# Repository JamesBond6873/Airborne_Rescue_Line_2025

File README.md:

<div align="center">

</div>

<br/>

<p align="center">
  This is the repository for <strong>Airborne</strong>, a Portuguese robotics team that participated in the
  <a href="https://junior.robocup.org/">RoboCup Junior</a> sub-league
  <a href="https://junior.robocup.org/rcj-rescue-line/">Rescue Line</a>.
</p>

# About the Competition
<p align="center"><i>
  "The land is too dangerous for humans to reach the victims. Your team has been given a challenging task. The robot must be able to carry out a rescue mission in a fully autonomous mode with no human assistance. The robot must be durable and intelligent enough to navigate treacherous terrain with hills, uneven land, and rubble without getting stuck. When the robot reaches the victims, it has to gently and carefully transport each one to the safe evacuation point where humans can take over the rescue. The robot should exit the evacuation zone after a successful rescue to continue its mission throughout the disaster scene until it leaves the site. Time and technical skills are essential!"
</i></p>

<div align="center">
  
</div>

# About the Robot

<!-- First block: Image on the left -->

<p align="justify">
  Our robot was built to reliably complete all challenges of the RoboCup Junior Rescue Line competition through a combination of computation, custom electronics, and mechanical design. It uses a dual-processor architecture: a Raspberry Pi 5 for high-level logic and AI, and a Raspberry Pi Pico for real-time control of motors and sensors. A Google Coral USB Accelerator enables onboard execution of two YOLOv8 models, one for victim detection and another for identifying the silver evacuation zone, which provide fast and accurate results compared to traditional computer vision.
</p>

<br/>

<!-- Second block: Image on the right -->

<p align="justify">
  The chassis was entirely designed in SolidWorks and 3D printed, with over 70 custom parts and a modular structure that simplifies maintenance. A tilt-mounted wide-angle camera, passive suspension system, and dual-servo rescue arm ensure strong performance across rough terrain. Internally, custom PCBs manage power distribution and sensor integration, keeping the system reliable and clean, with a much lower risk of lose wires. Software processes run in parallel for serial communication between boards, image processing, and control/decision-making, supported by a custom HTML/Websocket interface for real-time monitoring and debugging.
</p>

<br/>

<p align="center">
  As required by the competition <a href="https://github.com/JamesBond6873/Airborne_Rescue_Line_2025/blob/main/Documents/Rules/000_RoboCup_Junior_Rescue_Line_Rules_2025.pdf">rules</a>, in addition to this GitHub Repository, we created detailed documentation of the robot and our development process in the form of a <a href="https://github.com/JamesBond6873/Airborne_Rescue_Line_2025/blob/main/Documents/Final%20Rubrics/00_Airborne_TDP_RoboCup_Rescue_Line_2025.pdf">Technical Description Paper</a>, a <a href="https://github.com/JamesBond6873/Airborne_Rescue_Line_2025/blob/main/Documents/Final%20Rubrics/01_Airborne_Poster_RoboCup_Rescue_Line_2025.pdf">Technical Poster</a>, and a <a href="https://github.com/JamesBond6873/Airborne_Rescue_Line_2025/blob/main/Documents/Final%20Rubrics/02_Airborne_Video_RoboCup_Rescue_Line_2025_Compressed.mp4">Presentation Video</a>.
</p>

## 📂 Components

- Raspberry Pi 5 8GB Ram
- Raspberry Pi Pico
- Google Coral USB Accelerator
- Raspberry Pi Camera Module V3 Wide
- 5x VL53L0X ToF
- ICM-20948 9DOF IMU
- TCA9458 Multiplexer
- 4x Home-made Silicone Wheels
- 4x 12V 77RPM DC Geared Motors
- 4x 3S ESCs
- 6x SG90 MicroServos
- PCA9685 Servo Driver
- 2x Custom Led Bar PCB
- DRV8833 Power Driver
- Gens Ace 3S 2700mAh Lipo Battery
- D24V50F5 Step Down
- D36V28F5 Step Down

<br/>

## 🧠 Repository Structure

<p align="justify"> 
  This repository contains all the files developed and used throughout our RoboCup Junior Rescue Line project.
</p>

  - <code>RobotCode_Field_Version</code>: Contains the latest version of the code used in the official Field Runs
  - <code>RobotCode_TC_Version</code>: Contains the version used during the Technical Challenge run
  - <code>Ai</code>: Contains the versions of the YoloV8 Small Models used for victim and silver strip detections
  - <code>Documents</code>:
      - <code>Final Rubrics</code>: Contains our final three evaluated documents: Team Description Paper, Technical Poster and  Presentation Video (compressed)
      - <code>Rules</code>: Contains all official competition rulebooks (Rescue Line, Technical Challenge, SuperTeams), as well as the corresponding rubrics and templates for the documents
      - <code>scores</code>:  Contains the final scores from the RoboCup Junior World Championship 2025, in Salvador, Brazil

<br/>

# 🔗 Useful Links

- [Airborne Photo/Video Album](https://drive.google.com/drive/folders/1JC7H4FIJUuHvwdzJ9MUNMwsvkezMXKDg?usp=drive_link)
- [Technical Description Paper](https://drive.google.com/file/d/1SsVflj773ZcgajpcdkzmWjwUXBWZYv1-/view?usp=drive_link)
- [Technical Poster](https://drive.google.com/file/d/1fPJXqmR9CHxOLH45z3VVppOXiR5PiPfq/view?usp=drive_link)
- [Presentation Video](https://drive.google.com/file/d/1rCQD-FLG8RNpqSPlJDvGeZCaVhfCN_2y/view?usp=drive_link)
- [Rescue Line Rules 2025](https://github.com/JamesBond6873/Airborne_Rescue_Line_2025/blob/main/Documents/Rules/000_RoboCup_Junior_Rescue_Line_Rules_2025.pdf)
- [Airborne Instagram Account](https://www.instagram.com/airborne_2023/)

<br/>
<br/>

# 🤝 Sponsors

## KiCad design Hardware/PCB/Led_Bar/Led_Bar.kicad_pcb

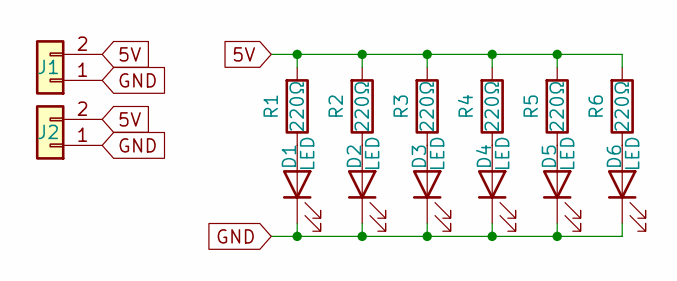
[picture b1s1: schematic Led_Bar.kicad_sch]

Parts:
D1, D2, D3, D4, D5, D6: LED; LED_D5.0mm
J1, J2: Conn_01x02; PinHeader_1x02_P2.54mm_Vertical
R1, R2, R3, R4, R5, R6: 220Ω; R_Axial_DIN0207_L6.3mm_D2.5mm_P2.54mm_Vertical

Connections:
5V: J1.2, J2.2, R1.2, R2.2, R3.2, R4.2, R5.2, R6.2
GND: D1.1 (K), D2.1 (K), D3.1 (K), D4.1 (K), D5.1 (K), D6.1 (K), J1.1, J2.1
unnamed: D1.2 (A), R1.1
unnamed: D2.2 (A), R2.1
unnamed: D3.2 (A), R3.1
unnamed: D4.2 (A), R4.1
unnamed: D5.2 (A), R5.1
unnamed: D6.2 (A), R6.1

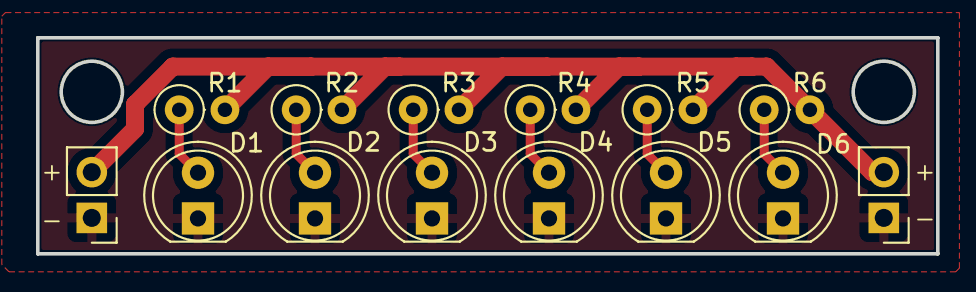
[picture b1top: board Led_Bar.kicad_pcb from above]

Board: 2 copper layers, 50.0 x 12.0 mm, 14 parts (0 on the bottom side), 8 nets.

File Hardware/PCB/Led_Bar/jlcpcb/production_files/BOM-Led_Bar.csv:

Comment,Designator,Footprint,LCSC,Quantity
220Ω,R6,R_Axial_DIN0207_L6.3mm_D2.5mm_P2.54mm_Vertical,,1
LED,D1,LED_D5.0mm,,1
220Ω,R1,R_Axial_DIN0207_L6.3mm_D2.5mm_P2.54mm_Vertical,,1
LED,D2,LED_D5.0mm,,1
220Ω,R2,R_Axial_DIN0207_L6.3mm_D2.5mm_P2.54mm_Vertical,,1
LED,D3,LED_D5.0mm,,1
220Ω,R3,R_Axial_DIN0207_L6.3mm_D2.5mm_P2.54mm_Vertical,,1
LED,D4,LED_D5.0mm,,1
220Ω,R4,R_Axial_DIN0207_L6.3mm_D2.5mm_P2.54mm_Vertical,,1
LED,D5,LED_D5.0mm,,1
220Ω,R5,R_Axial_DIN0207_L6.3mm_D2.5mm_P2.54mm_Vertical,,1
LED,D6,LED_D5.0mm,,1
Conn_01x02,J1,PinHeader_1x02_P2.54mm_Vertical,,1
Conn_01x02,J2,PinHeader_1x02_P2.54mm_Vertical,,1

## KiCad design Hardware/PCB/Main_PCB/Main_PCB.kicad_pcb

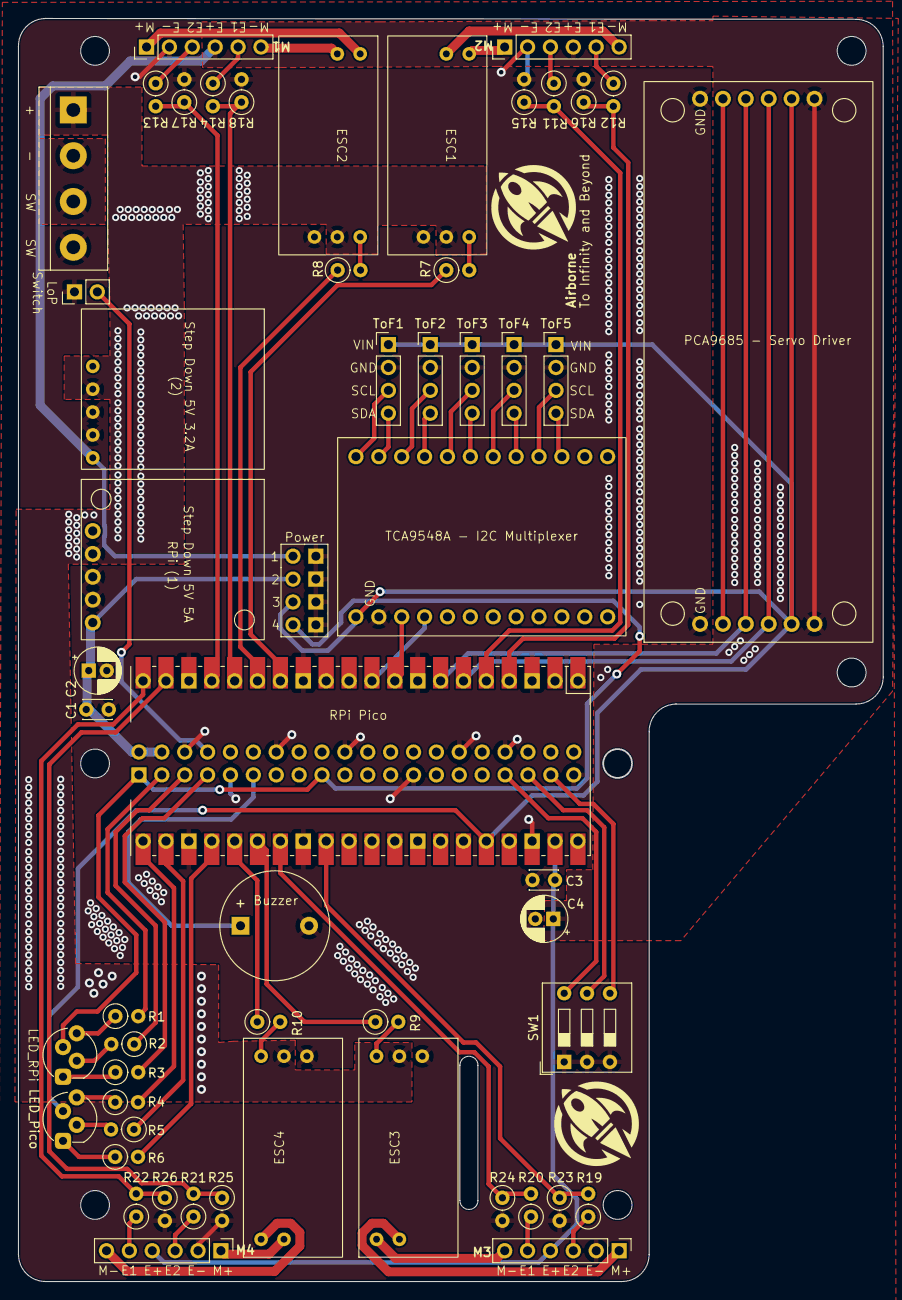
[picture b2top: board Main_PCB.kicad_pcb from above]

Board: 2 copper layers, 95.9 x 140.1 mm, 61 parts (1 on the bottom side), 70 nets.

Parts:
Buzzer1: Buzzer-Active
C1, C3: 100nF; C_Disc_D3.0mm_W2.0mm_P2.50mm
C2, C4: 10uF; CP_Radial_D5.0mm_P2.00mm
ESC1, ESC2, ESC3, ESC4: ESCs
J1: Battery & Power SW; Power_Switch_inputt
J3: PCA9685; PCA9685_Breakout
J4: Conn_01x02_Pin; PinHeader_1x02_P2.54mm_Vertical
LED_Pico: LED_RGAB; LED_D5.0mm-4_RGB_Staggered_Pins
LED_RPi: LED_RGAB; LED_D5.0mm-4_RGB_Staggered_Pins
M1, M2, M3, M4: PinHeader_Motor_Encoder
MH1, MH3, MH4, MH4#2, MH4#3: MountingHole_2.7mm_M2.5
Power1: Power_PinHeader_4
R1, R2, R3, R4, R5, R6: 220Ω; R_Axial_DIN0207_L6.3mm_D2.5mm_P2.54mm_Vertical
R7, R8, R9, R10, R11, R12, R13, R14, R19, R20, R21, R22: 1.2kΩ; R_Axial_DIN0207_L6.3mm_D2.5mm_P2.54mm_Vertical
R15, R16, R17, R18, R23, R24, R25, R26: 2kΩ; R_Axial_DIN0207_L6.3mm_D2.5mm_P2.54mm_Vertical
RPi Pico: Pico; RPi_Pico_SMD_TH
Raspberry Pi 5: GPIO; PinSocket_2x20_P2.54mm_Vertical
SW1: SW_DIP_x03; SW_DIP_SPSTx03_Slide_9.78x9.8mm_W7.62mm_P2.54mm
StepDown5V3.2A1: Step Down 5V 3.2A
StepDown5V5A1: Step_Down_5V_5A_D24V50F5
TCA9548A1: TCA9548A_Multiplexer_I2C
ToF1, ToF2, ToF3, ToF4, ToF5: ToF_VL53L0X

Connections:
1M1: ESC1.5 (M2), M1.1 (M+)
1M2: ESC1.4 (M1), M1.6 (M-)
2M1: ESC2.5 (M2), M2.1 (M+)
2M2: ESC2.4 (M1), M2.6 (M-)
3.3V: J3.5, LED_Pico.3 (A), Power1.5 (5V-1), RPi Pico.36 (3V3), TCA9548A1.1 (VIN), ToF1.1 (VIN), ToF2.1 (VIN), ToF3.1 (VIN), ToF4.1 (VIN), ToF5.1 (VIN)
3.3VRPI: LED_RPi.3 (A), Power1.7 (3.3Vrpi), Raspberry Pi 5.1, Raspberry Pi 5.17
3M1: ESC3.4 (M1), M3.1 (M+)
3M2: ESC3.5 (M2), M3.6 (M-)
4M1: ESC4.4 (M1), M4.1 (M+)
4M2: ESC4.5 (M2), M4.6 (M-)
5V-1: C1.1, C2.1, Power1.3 (3.3V), Raspberry Pi 5.2, Raspberry Pi 5.4, StepDown5V5A1.5 (OUT)
5V-2: C3.1, C4.1, J3.6, M1.4 (E+), M2.4 (E+), M3.4 (E+), M4.4 (E+), Power1.1 (5V-2), RPi Pico.39 (VSYS), StepDown5V3.2A1.1 (OUT)
Bat +: ESC1.2 (VCC), ESC2.2 (VCC), ESC3.2 (VCC), ESC4.2 (VCC), J1.1, StepDown5V3.2A1.4 (VIN), StepDown5V5A1.2 (VIN)
GND: Buzzer1.2 (-), C1.2, C2.2, C3.2, C4.2, ESC1.1 (GND), ESC2.1 (GND), ESC3.1 (GND), ESC4.1 (GND), J1.4, J3.1, J4.1, M1.2 (E-), M2.2 (E-), M3.2 (E-), M4.2 (E-), Power1.2 (GND1), Power1.4 (GND4), Power1.6 (GND2), Power1.8 (GND3), R15.2, R16.2, R17.2, R18.2, R23.2, R24.2, R25.2, R26.2, RPi Pico.3 (GND), RPi Pico.8 (GND), RPi Pico.13 (GND), RPi Pico.18 (GND), RPi Pico.23 (GND), RPi Pico.28 (GND), RPi Pico.38 (GND), Raspberry Pi 5.6, Raspberry Pi 5.9, Raspberry Pi 5.14, Raspberry Pi 5.20, Raspberry Pi 5.25, Raspberry Pi 5.30, Raspberry Pi 5.34, Raspberry Pi 5.39, SW1.1, SW1.2, SW1.3, StepDown5V3.2A1.2 (GND), StepDown5V3.2A1.3 (GND), StepDown5V5A1.3 (GND), StepDown5V5A1.4 (GND), TCA9548A1.2 (GND), ToF1.2 (GND), ToF2.2 (GND), ToF3.2 (GND), ToF4.2 (GND), ToF5.2 (GND)
GPIO2: R1.2, Raspberry Pi 5.3
GPIO2P: R12.2, R16.1, RPi Pico.4 (GPIO2)
GPIO3: R2.1, Raspberry Pi 5.5
GPIO3P: R11.2, R15.1, RPi Pico.5 (GPIO3)
GPIO4: R3.2, Raspberry Pi 5.7
GPIO4P: J3.4, RPi Pico.6 (GPIO4)
GPIO5P: J3.3, RPi Pico.7 (GPIO5)
GPIO6P: RPi Pico.9 (GPIO6), TCA9548A1.3 (SDA)
GPIO7P: RPi Pico.10 (GPIO7), TCA9548A1.4 (SCL)
GPIO10P: R7.1, RPi Pico.14 (GPIO10)
GPIO11P: R8.1, RPi Pico.15 (GPIO11)
GPIO12P: R14.2, R18.1, RPi Pico.16 (GPIO12)
GPIO13: Raspberry Pi 5.33, SW1.6
GPIO13P: R13.2, R17.1, RPi Pico.17 (GPIO13)
GPIO14: J4.2, Raspberry Pi 5.8
GPIO14P: R21.2, R25.1, RPi Pico.19 (GPIO14)
GPIO15P: R22.2, R26.1, RPi Pico.20 (GPIO15)
GPIO16P: R4.2, RPi Pico.21 (GPIO16)
GPIO17: Buzzer1.1 (+), Raspberry Pi 5.11
GPIO17P: R5.1, RPi Pico.22 (GPIO17)
GPIO18P: R6.2, RPi Pico.24 (GPIO18)
GPIO19: Raspberry Pi 5.35, SW1.5
GPIO19P: R10.1, RPi Pico.25 (GPIO19)
GPIO20P: R9.1, RPi Pico.26 (GPIO20)
GPIO21P: R20.2, R24.1, RPi Pico.27 (GPIO21)
GPIO22P: R19.2, R23.1, RPi Pico.29 (GPIO22)
GPIO26: Raspberry Pi 5.37, SW1.4
unnamed: LED_RPi.4 (BK), R1.1
unnamed: LED_RPi.2 (GK), R2.2
unnamed: LED_RPi.1 (RK), R3.1
unnamed: LED_Pico.4 (BK), R4.1
unnamed: LED_Pico.2 (GK), R5.2
unnamed: LED_Pico.1 (RK), R6.1
unnamed: ESC1.3 (PWM), R7.2
unnamed: ESC2.3 (PWM), R8.2
unnamed: ESC3.3 (PWM), R9.2
unnamed: ESC4.3 (PWM), R10.2
unnamed: J1.2, J1.3
unnamed: M1.5 (E1), R12.1
unnamed: M1.3 (E2), R11.1
unnamed: M2.5 (E1), R14.1
unnamed: M2.3 (E2), R13.1
unnamed: M3.5 (E1), R20.1
unnamed: M3.3 (E2), R19.1
unnamed: M4.5 (E1), R22.1
unnamed: M4.3 (E2), R21.1
SCL_T1: TCA9548A1.13 (SC7), ToF1.3 (SCL)
SCL_T2: TCA9548A1.15 (SC6), ToF2.3 (SCL)
SCL_T3: TCA9548A1.17 (SC5), ToF3.3 (SCL)
SCL_T4: TCA9548A1.19 (SC3), ToF4.3 (SCL)
SCL_T5: TCA9548A1.21 (SC3), ToF5.3 (SCL)
SDA_T1: TCA9548A1.14 (SD7), ToF1.4 (SDA)
SDA_T2: TCA9548A1.16 (SD6), ToF2.4 (SDA)
SDA_T3: TCA9548A1.18 (SD5), ToF3.4 (SDA)
SDA_T4: TCA9548A1.20 (SD4), ToF4.4 (SDA)
SDA_T5: TCA9548A1.22 (SD3), ToF5.4 (SDA)

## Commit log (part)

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2025-02-04 Francisco: Added proper main loop time control (set to 10ms)
2025-02-04 Francisco: Removed time delays on RPi Pick/Release balls for test purposes
2025-02-04 Francisco: Fixed "Object not callable" ser.in_waiting() to ser.in_waiting
2025-02-04 Francisco: Added debug print for not functional "Ok" receiver
2025-02-04 Francisco: --Test-- Created sendSerialResponse to do the full procedure alone with message resend
2025-02-04 Francisco: Removed prints from RPi Pico ArmGrip for further wait Response testing
2025-02-04 Francisco: Fixed interpreter error: takes 3 positional arguments, only 2 were...
2025-02-04 Francisco: Found bug in readSerial RPi/main.py (neglecting serial port) if ser.in_waiting <= 0: instead of >
2025-02-04 Francisco: Attempt to solve motor uncontrollable after arm/ball commands
2025-02-04 Francisco: --Test-- Attempt 2
2025-02-05 Francisco: Added old code to Software Test
2025-02-05 Francisco: New Attempt
2025-02-05 Francisco: Fixed test bug
2025-02-05 Francisco: Fixed bug in test
2025-02-05 Francisco: Test Attempt
2025-02-05 Francisco: Went back to functional?!
2025-02-05 Francisco: Setting Debug to False...
2025-02-05 Francisco: Attempt to fix logic problem
2025-02-05 Francisco: sendSerial() clean up, removed need for debug argument
2025-02-05 Francisco: More Clean Up
2025-02-09 Francisco: Created In Progress Directory
2025-02-09 Francisco: Modified softDebug information (moved to DEBUG exclusive)
2025-02-09 Francisco: Added new stable release with new Debug and SoftDebug Functionalities
2025-02-10 Francisco: Fixed motor not stopping bug
2025-02-10 Francisco: Added gitignore for pycache
2025-02-10 Francisco: Deleted Pycache test
2025-02-10 Francisco: Created interpretMessage in robot.py
2025-02-10 Francisco: Added Camera Interactions through gamepad.py
2025-02-10 Francisco: --Test-- Fixing Bug
2025-02-10 Francisco: Fixed interpretMessage(), copied properly previous stableRelease
2025-02-10 Francisco: Removed Not needed debug prints
2025-02-10 Francisco: New Stable Release, without duplicate code, and camera gamepad interface implemented
2025-02-10 Francisco: Added delay for camera servo to get to desire position
2025-02-10 Francisco: Attempt to only allow for one motor arm per pico "life"
2025-02-12 Francisco: New Stable Release
2025-02-12 Francisco: Fixed variable definition problem
2025-02-12 Francisco: Added example control.py and line_cam.py files
2025-02-12 Francisco: Added mp_manager.py for tests
2025-02-12 Francisco: Still a test...
2025-02-12 Francisco: Crazy attempt
2025-02-15 Francisco: Cleaned Pychaches
2025-02-15 Transformed Gamepad.py in a process
2025-02-15 Francisco: Layed Out line following Code
2025-02-15 Francisco: Camera working -low quality through ssh
2025-02-16 Francisco: Testing Colour Picker
2025-02-16 Francisco: Tested successfully LoP switch on/off
2025-02-17 Francisco: Functional with no Buzzer
2025-02-22 Francisco: Only LoP Switch Attempt
2025-02-22 Francisco: Created control loop in robot.py and Mu ltiprocessing Manager
2025-02-22 Francisco: Attempt at simple lineFollowing
2025-03-01 Francisco: Started isolated LineAngle Processing
2025-03-01 Francisco: Ready for frames collection
2025-03-01 Francisco: Added angle to cv2_image
2025-03-02 Francisco: Testing moments (centroid and line angle)
2025-03-02 Francisco: Created new stable release with line following (centroid + lineAngle)
2025-03-02 Francisco: Intersection detection Functional?
2025-03-03 Francisco: Updated In Progress 2 to last stable release
2025-03-03 Francisco: Fixed bad return to stable release IP2
2025-03-03 Francisco: Added "last" variables updates
2025-03-03 Francisco: test removing from black, green image
2025-03-04 Francisco: Created new InProgress3
2025-03-04 Francisco: Functional Line Following
2025-03-04 Francisco: Ready for Stable Release
2025-03-04 Francisco: Calibrated maxlinewidth and blackTop
2025-03-07 Francisco: Cv2.Resize + improved interpretPOI
2025-03-10 Francisco: New Stable_Release_03102025_1531 (7 Point Line Following + Intersections (no uTurn yet)
2025-03-10 Francisco: Intersection uTurn
2025-03-11 Francisco: New Stable Release (Line + Intersections + Basic Gap + Red Strip)
2025-03-11 Francisco: Increased Line Frame Rate to 40FPS
2025-03-11 Francisco: Mid Work commit
2025-03-16 Francisco: Added erode and dilate to image capture
2025-04-01 Francisco: Fixed Git on Rpi
2025-04-01 Francisco: Almost ready for stable release
2025-04-03 Francisco: Fixing lack of line_cam file
2025-04-03 Francisco: test day commit
2025-04-05 Francisco: After normal runs commit
2025-04-05 Francisco: Created copy of competition code
2025-04-14 Francisco: Pre-Work commit
2025-04-15 Francisco: mixed late commit
2025-04-17 Francisco: Updated Code for new Ai-Victim Detection test
2025-04-17 Francisco: Git fix
2025-04-17 Francisco: One More fix...
2025-04-20 Francisco: ToF Sensors Integration Tests
2025-04-25 Francisco: New attempt at properly exported victim detection model
2025-04-25 Francisco: New attempt at custom trained yolov8 model
2025-04-25 Francisco: Net attempt model tflite with metadata incorporated
2025-04-25 Francisco: Got custom YoloV8 model running
2025-04-26 Francisco: Commit prior changes
2025-04-26 Francisco: Added a command line reader thread
2025-04-26 Francisco: New CLI commands exit, list, motor, LOP
2025-04-26 Francisco: New CLI commands objective, vars, EZstatus
2025-04-27 Francisco: Implemented average values for ball pickup
2025-04-28 Francisco: Almost functional Ball Picking (requires testing)
2025-05-01 Francisco: 3 Ball Pick Up Sucessful
2025-05-11 Francisco: Created DataSet of Evacuation Zone
2025-05-11 Francisco> Late Work Commit - Not tested drop victim algorithm
2025-05-17 Francisco: Debugging and slight fixes need to deposit functions
2025-05-17 Francisco: Made serial prints selective in config. Added additional command based debug information
2025-05-18 Francisco: Evacuation Zone Values Calibration
2025-05-18 Francisco: Color Calibration Data
2025-05-19 Francisco: Captured new dataset, some settings changed
2025-05-19 Francisco: Created basic web socket and html page for live data streaming
2025-05-25 Francisco: Clean Up of older folders/files
2025-05-25 Francisco: Updated InProgress to last stable release
2025-05-25 Francisco: Reorganized Git 2
2025-05-25 Francisco: Improved Index.html
2025-06-02 Francisco: Updated pins for new PCB
2025-06-04 Francisco: Code compatible with IMU data
2025-06-07 Francisco: Functional ToF with Multiplexer Code
2025-06-07 Francisco: ToF with Multiplexer Functional Code
2025-06-07 Francisco: IMU data class clean up
2025-06-07 Francisco: Final command to get IMU and ToF Data
2025-06-07 Francisco: Communication Clean Up
2025-06-08 Francisco: Not Initialized Sensors Bug Fix (now Independent)
2025-06-08 Francisco: Fixed 2 Line Sensor Data Bug
2025-06-08 Francisco: Updated HTML Robot Page to contain IMU and ToF data
2025-06-08 Francisco: Ready for ramp detection tests
2025-06-08 Francisco: New Silver Strip Model
2025-06-08 Francisco: Semi-Functional Silver Line Detection
2025-06-08 Francisco: Improved HTML Robot UI
2025-06-08 Francisco: Fixed ToF Hang Bug
2025-06-09 Francisco: Clean Up
2025-06-09 Francisco: New Full Run DataSet
2025-06-11 Francisco: Progress interpret Poi
2025-06-11 Francisco: Updated line crop values
2025-06-13 Francisco: HTML Page UI update
2025-06-13 Francisco: Added Custom IP connection to HTML Page
2025-06-13 Francisco: Added Variable Ramp Speed
2025-06-13 Francisco: Code Cleaning
2025-06-13 Francisco: Code Cleaning 3
2025-06-13 Francisco: Updated HTML Page Variable Names
2025-06-14 Francisco: Mid work gap controller not functional
2025-06-16 Francisco: Gap Controller Added - Requires Testing
2025-06-28 Francisco: Gap Improvement and Silver Angle Detection
2025-06-29 Francisco: Implemented Ready To Enter Zone
2025-07-01 Francisco: UI HTML Page update
2025-07-01 Francisco: Silver Line Backwards movement for orientation (requires testing)
2025-07-01 Francisco: Added time after deposit condition and variables
2025-07-01 Francisco: Set code to robot testing
2025-07-01 Francisco: Attempt at creating requirements.txt
2025-07-01 Francisco: Fixed bug not going forward on zone after victim drop
2025-07-01 Francisco: Added camServoAngle to have camera adjustment in ramp
2025-07-01 Francisco: Modified UI HTML Page
2025-07-01 Francisco: Fixed bug with double ball pickup
2025-07-01 Francisco: latest frames
2025-07-02 Francisco: Average POI and POI No Crop for earlier turns (requires testing)
2025-07-02 Francisco: Added silverLineDetected reset to False
2025-07-02 Francisco: Added cooldown timer for pickVictim to avoid double picks
2025-07-02 Francisco: Fixed bug in interpretPoi black on both sides (wrong angle, needed to be normalized)
2025-07-03 Francisco: Fixed bug with blocking sensor data request
2025-07-03 Francisco: Improved sensor data parser to allow for inverted message lines
2025-07-03 Francisco: Improved UI HTML Page
2025-07-03 Francisco: Increased victim pick cooldown (8s) to avoid double picks and silverline ready to enter is set to true if no line is detected
2025-07-03 Francisco: Incorporated a second black color threshold dedicated to the top of the image
2025-07-04 Francisco: Added average to red line detection and fixed wait time (not permanent)
2025-07-04 Francisco: Mid work commit, evac zone entry
2025-07-05 Francisco: Finished evac zone entry based on walls closer (requires testing)
2025-07-05 Francisco: Simple pre test updates
2025-07-05 Francisco: Added LOP block to red line controller
2025-07-05 Francisco: Improved seesaw detection with average and calibrated times/values
2025-07-07 Francisco: entry zone fix (tof values states and angles calibration)
2025-07-07 Francisco: Fixed bugs in entry zone function
2025-07-07 Francisco: Added waiting phase for successful pick to improve reliability
2025-07-07 Francisco: Found bug with waiting for pick timer
2025-07-07 Francisco: Created setup to easily acquire silver dataSet
2025-07-07 Francisco: Improvements to easy silver line dataset acquisition
2025-07-08 Francisco: New Silver Strip Classification AI Models (dataset V4)
2025-07-08 Francisco: Updated line cam process to deal with exit needs
2025-07-08 Francisco: Fixed bug with rotation speed after deposit and saving images in the wrong folder
2025-07-08 Francisco: Went Back to previous AI model and fixed bug with exit aligned with wall wrong variable
2025-07-08 Francisco: Added a check to avoid saying we alligned when we are not close to the wall (facing away from it)
2025-07-08 Francisco: Fixed typo in aligned condition
2025-07-09 Francisco: Robot Lights now start off (after 1s on)
2025-07-09 Francisco: Pico stops motors after closing hand on the correct position
2025-07-09 Francisco: Implemented New V9 Model
2025-07-09 Francisco: Removed duplicate line function and added area print debug
2025-07-10 Francisco: Updated line cam to use most recent silver strip model
2025-07-10 Francisco: Added failsafe in case the edgetpu model fails to load (try again)
2025-07-10 Francisco: Created new silver dataset for orientation pre-entry
2025-07-10 Francisco: Silver Strip Detection/Control, Ready to test
2025-07-10 Francisco: Exit bug fixing
2025-07-10 Francisco: Brough back sensor request data timeout (35ms)
2025-07-12 Francisco: Fixed "return" bug that crashed robot when picking ball
2025-07-12 Francisco: Mid exit development commit - testing
2025-07-13 Francisco: Stable Release (with full evac zone) :) Requires bug hunting for multiple evac zone entries and arm position fdix
2025-07-13 Francisco: Misc
2025-07-13 Francisco: Stable Release (full evac zone)
2025-07-13 Francisco: Still Functional (minor Tweaks)
2025-07-15 Francisco: Created folder for final robot code
2025-07-24 Francisco: Improved color picker script (image calibration)
2025-07-24 Removed: Token file, in progress folders and python version file
2025-07-24 Removed coral useless folder
2025-07-24 Moved Dataset practice images to head folder
2025-07-24 Added last used version of robot code for field runs
2025-07-24 Added last used version of robot code for the technical challenge
2025-07-25 Update README.md - Still not finished
